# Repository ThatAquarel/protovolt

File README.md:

[![ProtoV MINI][cover]][website]

# A power supply to catalyze prototyping

[![Release][release-badge]][release]
[![CI][ci-badge]][ci]
[![Chat][chat-badge]][chat]
[![Crowd Supply][cs-badge]][cs]

**ProtoV MINI** is a credit card-sized, dual-channel lab power supply for
electronics prototyping and field testing. It is powered by USB-C PD and runs
open firmware written in Rust.

## Getting Started

Start with the [quick-start guide](docs/quick_start.md) to connect a USB-C PD
power supply, optionally link ProtoV MINI to a computer, and open
[ProtoV App](https://protov.app).

## Development

```sh
git clone https://github.com/flakeblade/protov.git
cd protov
rustup target add thumbv6m-none-eabi
cargo install just
just build
```
See [development](#development-1) for prerequisites, tests, and common
commands. Run `just --list` to see every available recipe.

## Documentation

### Guides

- [Device overview](docs/product.md) — hardware overview, and dimensions
- [Quick start](docs/quick_start.md) — quickstart wiring guide
- [Interface guide](docs/interface_guide.md) — normal UI flow with example screens
- [Troubleshooting](docs/troubleshooting.md) — faults, protection, and boot failures

### Development

Project structure
- [Repository index, and workspace modules](docs/repository.md)
- [Firmware roadmap](docs/roadmap.md)

Installation, building, and uploading
1. [Toolchain installation, and building](docs/development.md)
2. [Release bundling, and firmware signature](docs/releases.md)
3. [Flashing to hardware](docs/flashing.md)

### References

Hardware compatibility
- [Power delivery sources](docs/compatibility.md)
- [Breadboards](docs/compatibility.md)

Design documentation
- [Hardware and dimensions](docs/hardware.md)
- [SCPI protocol reference](protov-scpi/PROTOCOL.md)

Support
- [Troubleshooting](docs/troubleshooting.md)

<!-- - [Product overview](docs/product.md)
    
- [Flashing](docs/flashing.md)

- [SCPI protocol](protov-scpi/PROTOCOL.md)
- [SCPI crate](protov-scpi/README.md)
- [Bootloader](protov-bootloader/README.md)
- [Flash layout and firmware verification](protov-nvm/README.md) -->

## Contributing

Bug reports and contributions are welcome in the
[GitHub repository](https://github.com/flakeblade/protov).

> [!WARNING]
> Modifying or uploading firmware is done entirely at your own risk. An
> incompatible image can leave the device inoperable and may require USB
> BOOTSEL or SWD recovery. Bypassing current, voltage, temperature, power, or
> other protection limits can damage ProtoV MINI, connected equipment, or
> wiring and may create an electrical or fire hazard. Verify the hardware
> revision, understand every safety-related change, and test conservatively.

## License

[Eclipse Public License 2.0](LICENSE) © Alex Xia — [@ThatAquarel](http://github.com/thataquarel)

<p align="center">
  
  <br>
  A Flake &amp; Blade Robotics Design project
</p>

[fbrd]: https://flakeblade.com
[release-badge]: https://github.com/flakeblade/protov/actions/workflows/release.yml/badge.svg
[release]: https://github.com/flakeblade/protov/actions/workflows/release.yml
[ci-badge]: https://github.com/flakeblade/protov/actions/workflows/ci.yml/badge.svg
[ci]: https://github.com/flakeblade/protov/actions/workflows/ci.yml
[chat-badge]: https://img.shields.io/badge/chat-discussions-success.svg
[chat]: https://github.com/flakeblade/protov/discussions
[cs-badge]: https://img.shields.io/badge/Crowd-Supply-099?labelColor=555
[cs]: https://www.crowdsupply.com/flake-and-blade-robotics-design/protov-mini
[cover]: docs/res/logo/protov_mini_cover.svg
[website]: https://protov.app

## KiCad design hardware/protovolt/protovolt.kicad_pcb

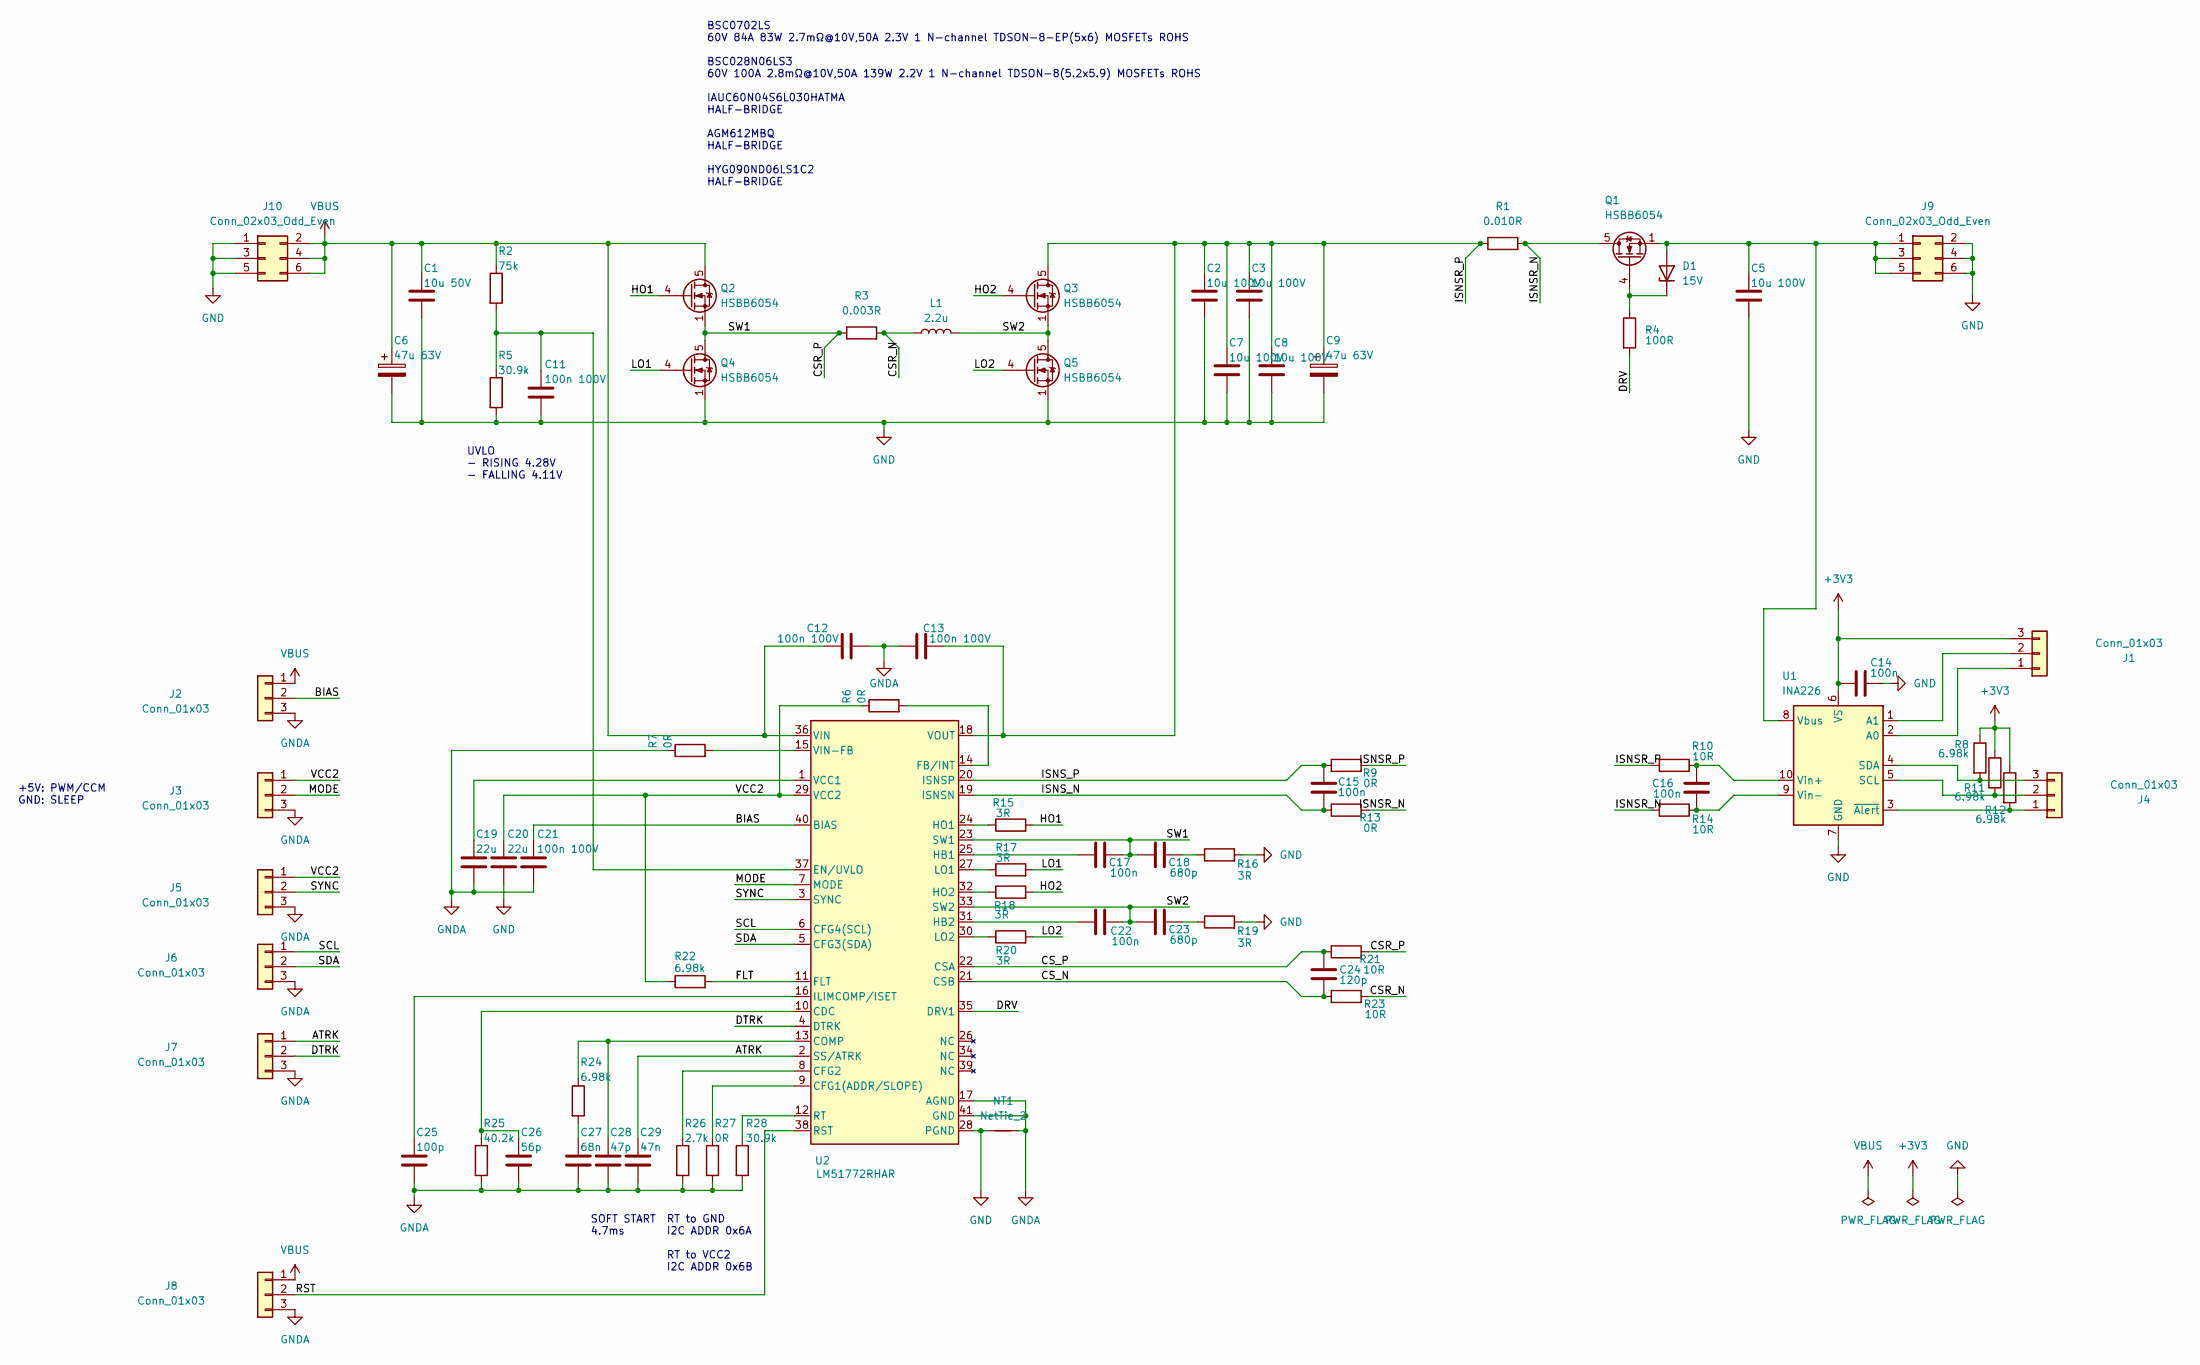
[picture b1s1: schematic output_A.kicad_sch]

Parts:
C1: 10u 50V; C_0805_2012Metric; LCSC C440198
C2, C3, C5, C7, C8: 10u 100V; C_1210_3225Metric; LCSC C5156756
C6, C9: 47u 63V; CP_Elec_8x10.5; LCSC C5246568
C11, C12, C13, C21: 100n 100V; C_0402_1005Metric; LCSC C162178
C14, C15, C16, C17, C22: 100n; C_0402_1005Metric; LCSC C77020
C18, C23: 680p; C_0402_1005Metric; LCSC C107030
C19, C20: 22u; C_0402_1005Metric; LCSC C3845593
C24: 120p; C_0402_1005Metric; LCSC C440165
C25: 100p; C_0402_1005Metric; LCSC C1546
C26: 56p; C_0402_1005Metric; LCSC C1572
C27: 68n; C_0402_1005Metric; LCSC C354977
C28: 47p; C_0402_1005Metric; LCSC C1567
C29: 47n; C_0402_1005Metric; LCSC C82219
D1: 15V; D_SOD-523; LCSC C131800
J1, J2, J3, J4, J5, J6, J7, J8: Conn_01x03; PinHeader_1x03_P2.54mm_Vertical_SMD_Pin1Left; LCSC C2883760
J9, J10: Conn_02x03_Odd_Even; PinHeader_2x03_P2.54mm_Vertical_SMD; LCSC C3294461
L1: 2.2u; L_Changjiang_FXL1050; LCSC C5359259
NT1: NetTie_2; NetTie-2_SMD_Pad0.5mm
Q1, Q2, Q3, Q4, Q5: HSBB6054; Diodes_PowerDI3333-8; LCSC C5341686
R1: 0.010R; R_2512_6332Metric_SHUNT; LCSC C393070
R2: 75k; R_0402_1005Metric; LCSC C286566
R3: 0.003R; R_2512_6332Metric_SHUNT; LCSC C326610
R4: 100R; R_0402_1005Metric; LCSC C25138
R5, R28: 30.9k; R_0402_1005Metric; LCSC C310222
R6, R7, R9, R13, R27: 0R; R_0402_1005Metric; LCSC C21376
R8, R11, R12, R22, R24: 6.98k; R_0402_1005Metric; LCSC C47500
R10, R14, R21, R23: 10R; R_0402_1005Metric; LCSC C25139
R15, R16, R17, R18, R19, R20: 3R; R_0402_1005Metric; LCSC C321179
R25: 40.2k; R_0402_1005Metric; LCSC C25893
R26: 2.7k; R_0402_1005Metric; LCSC C25885
U1: INA226; VSSOP-10_3x3mm_P0.5mm; LCSC C49851
U2: LM51772RHAR; QFN-40-1EP_6x6mm_P0.5mm_EP4.6x4.6mm_ThermalVias; LCSC C41383743

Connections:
+3V3: C14.1, J1.3, R8.1, R11.1, R12.1, U1.6 (VS)
/output_A/ATRK: C29.1, J7.1, U2.2 (SS/ATRK)
/output_A/BIAS: C21.2, J2.2, U2.40 (BIAS)
/output_A/CSR_N: L1.1, R3.2, R23.2
/output_A/CSR_P: C17.2, C18.1, Q2.1 (S), Q2.2 (S), Q2.3 (S), Q4.5 (D), R3.1, R21.2, U2.23 (SW1)
/output_A/CS_N: C24.2, R23.1, U2.21 (CSB)
/output_A/CS_P: C24.1, R21.1, U2.22 (CSA)
/output_A/DRV: R4.2, U2.35 (DRV1)
/output_A/DTRK: J7.2, U2.4 (DTRK)
/output_A/FLT: R22.2, U2.11 (FLT)
/output_A/HO1: Q2.4 (G), R15.2
/output_A/HO2: Q3.4 (G), R18.2
/output_A/ISNSR_N: Q1.5 (D), R1.2, R13.2, R14.2
/output_A/ISNSR_P: C2.1, C3.1, C7.1, C8.1, C9.1, C13.1, Q3.5 (D), R1.1, R9.2, R10.2, U2.18 (VOUT)
/output_A/ISNS_N: C15.1, R13.1, U2.19 (ISNSN)
/output_A/ISNS_P: C15.2, R9.1, U2.20 (ISNSP)
/output_A/LO1: Q4.4 (G), R17.2
/output_A/LO2: Q5.4 (G), R20.2
/output_A/MODE: J3.2, U2.7 (MODE)
/output_A/RST: J8.2, U2.38 (RST)
/output_A/SCL: J6.1, U2.6 (CFG4(SCL))
/output_A/SDA: J6.2, U2.5 (CFG3(SDA))
/output_A/SW2: C22.2, C23.1, L1.2, Q3.1 (S), Q3.2 (S), Q3.3 (S), Q5.5 (D), U2.33 (SW2)
/output_A/SYNC: J5.2, U2.3 (SYNC)
/output_A/VCC2: C20.1, J3.1, J5.1, R6.1, R22.1, U2.29 (VCC2)
GND: C1.2, C2.2, C3.2, C5.2, C6.2, C7.2, C8.2, C9.2, C11.1, C14.2, C20.2, J9.2, J9.4, J9.6, J10.1, J10.3, J10.5, NT1.1, Q4.1 (S), Q4.2 (S), Q4.3 (S), Q5.1 (S), Q5.2 (S), Q5.3 (S), R5.2, R16.2, R19.2, U1.7 (GND), U2.28 (PGND)
GNDA: C12.1, C13.2, C19.2, C21.1, C25.2, C26.2, C27.2, C28.2, C29.2, J2.3, J3.3, J5.3, J6.3, J7.3, J8.3, NT1.2, R7.1, R25.2, R26.2, R27.2, R28.2, U2.17 (AGND), U2.41 (GND)
unnamed: C18.2, R16.1
unnamed: C23.2, R19.1
unnamed: C27.1, R24.2
unnamed: C5.1, D1.2 (A), J9.1, J9.3, J9.5, Q1.1 (S), Q1.2 (S), Q1.3 (S), U1.8 (Vbus)
unnamed: D1.1 (K), Q1.4 (G), R4.1
unnamed: J1.1, U1.2 (A0)
unnamed: J1.2, U1.1 (A1)
unnamed: J4.1, R12.2, U1.3 (~Alert)
unnamed: J4.2, R11.2, U1.5 (SCL)
unnamed: J4.3, R8.2, U1.4 (SDA)
unnamed: C16.1, R10.1, U1.10 (Vin+)
unnamed: C16.2, R14.1, U1.9 (Vin-)
unnamed: C26.1, R25.1, U2.10 (CDC)
unnamed: R27.1, U2.9 (CFG1(ADDR/SLOPE))
unnamed: R26.1, U2.8 (CFG2)
unnamed: C28.1, R24.1, U2.13 (COMP)
unnamed: C11.2, R2.2, R5.1, U2.37 (EN/UVLO)
unnamed: R6.2, U2.14 (FB/INT)
unnamed: C17.1, U2.25 (HB1)
unnamed: C22.1, U2.31 (HB2)
unnamed: R15.1, U2.24 (HO1)
unnamed: R18.1, U2.32 (HO2)
unnamed: C25.1, U2.16 (ILIMCOMP/ISET)
unnamed: R17.1, U2.27 (LO1)
unnamed: R20.1, U2.30 (LO2)
unnamed: R28.1, U2.12 (RT)
unnamed: C19.1, U2.1 (VCC1)
unnamed: R7.2, U2.15 (VIN-FB)
VBUS: C1.1, C6.1, C12.2, J2.1, J8.1, J10.2, J10.4, J10.6, Q2.5 (D), R2.1, U2.36 (VIN)

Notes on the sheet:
UVLO - RISING 4.28V - FALLING 4.11V
+5V: PWM/CCM GND: SLEEP
SOFT START 4.7ms
BSC0702LS 60V 84A 83W 2.7mΩ@10V,50A 2.3V 1 N-channel TDSON-8-EP(5x6) MOSFETs ROHS BSC028N06LS3 60V 100A 2.8mΩ@10V,50A 139W 2.2V 1 N-channel TDSON-8(5.2x5.9) MOSFETs ROHS IAUC60N04S6L030HATMA HALF-BRIDGE AGM612MBQ HALF-BRIDGE HYG090ND06LS1C2 HALF-BRIDGE
RT to GND I2C ADDR 0x6A RT to VCC2 I2C ADDR 0x6B

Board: 4 copper layers, 75 parts (0 on the bottom side), 56 nets, no tracks yet.

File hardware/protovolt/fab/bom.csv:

"Id";"Designator";"Footprint";"Quantity";"Designation";"Supplier and ref";
1;"R4";"R_0402_1005Metric";1;"100R";;;
2;"J2,J8,J3,J4,J5,J7,J6,J1";"PinHeader_1x03_P2.54mm_Vertical_SMD_Pin1Left";8;"Conn_01x03";;;
3;"C29";"C_0402_1005Metric";1;"47n";;;
4;"J9,J10";"PinHeader_2x03_P2.54mm_Vertical_SMD";2;"Conn_02x03_Odd_Even";;;
5;"R19,R18,R17,R15,R16,R20";"R_0402_1005Metric";6;"3R";;;
6;"C23,C18";"C_0603_1608Metric";2;"680p";;;
7;"C20,C19";"C_0603_1608Metric";2;"22u";;;
8;"C13,C21,C11,C12";"R_0603_1608Metric";4;"100n 100V";;;
9;"Q1,Q4,Q5,Q3,Q2";"TDSON-8-1";5;"BSC0702LS";;;
10;"C5,C2,C7,C8,C4,C1,C3";"C_1210_3225Metric";7;"10u 100V";;;
11;"C27";"C_0402_1005Metric";1;"68n";;;
12;"R6,R9,R13,R27,R7";"R_0402_1005Metric";5;"0R";;;
13;"C16,C17,C22,C15,C14";"C_0603_1608Metric";5;"100n";;;
14;"R5,R28";"R_0402_1005Metric";2;"30.9k";;;
15;"C28";"C_0402_1005Metric";1;"47p";;;
16;"L1";"L_Changjiang_FXL1050";1;"2.2u";;;
17;"R1";"R_2512_6332Metric";1;"0.010R";;;
18;"R11,R22,R8,R12,R24";"R_0402_1005Metric";5;"6.98k";;;
19;"U1";"VSSOP-10_3x3mm_P0.5mm";1;"INA226";;;
20;"R26";"R_0402_1005Metric";1;"2.7k";;;
21;"U2";"QFN-40-1EP_6x6mm_P0.5mm_EP4.6x4.6mm_ThermalVias";1;"LM51772RHAR";;;
22;"R25";"R_0402_1005Metric";1;"40.2k";;;
23;"R21,R10,R14,R23";"R_0402_1005Metric";4;"10R";;;
24;"R2";"R_0402_1005Metric";1;"75k";;;
25;"R3";"R_1206_3216Metric";1;"0.003R";;;
26;"C24";"C_0402_1005Metric";1;"120p";;;
27;"D1";"D_SOD-123";1;"15V";;;
28;"C10,C9,C6";"CP_Elec_8x11.9";3;"39u 50V";;;
29;"C25";"C_0402_1005Metric";1;"100p";;;
30;"C26";"C_0402_1005Metric";1;"56p";;;

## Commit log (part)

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2025-05-11 kicad .gitignore
2025-05-11 add file to .gitignore
2025-05-11 LM51772 buck/boost base
2025-05-14 finish demo schematic
2025-05-15 route h-bridge
2025-05-15 fet routing
2025-05-16 four layer
2025-05-16 wire all
2025-05-16 route ground
2025-05-17 finalize DRU & PCB
2025-05-17 pnp files
2025-05-17 replace parts
2025-05-18 retrace all
2025-05-18 add BOM
2025-05-18 add basic parts
2025-05-19 order batch
2025-05-19 cleanup source
2025-05-19 implement TPS55289
2025-06-03 mini
2025-06-05 add interface & RP2040
2025-06-07 RP2040 boilerplate + INA226
2025-06-07 boost converter management
2025-06-07 render on screen test
2025-06-08 interface
2025-06-08 finalize parts in schematic
2025-06-09 route most
2025-06-09 ERC run
2025-06-09 assign footprints & LCSC id
2025-06-09 build all footprints
2025-06-09 import to PCB
2025-06-09 place ui elements
2025-06-10 route power stage
2025-06-10 route
2025-06-11 route digitals
2025-06-11 place all parts
2025-06-11 route simple traces
2025-06-11 route sense lines
2025-06-12 put FPC to front & rearrange buck/boost
2025-06-12 route power
2025-06-14 reroute all except 3V3 & GND
2025-06-16 finish routing
2025-06-16 all DRC except silkscreen warnings
2025-06-16 fix diode footprint
2025-06-16 finalize routing
2025-06-16 add logo
2025-06-16 cleanup schematic
2025-06-18 refactor
2025-06-21 first draft
2025-06-21 first display
2025-06-21 dynamic text render without clear
2025-06-21 first fab run
2025-06-21 add transparent logo
2025-06-22 ui rendering + updating
2025-06-22 simplify controls drawing
2025-06-22 temporary dev directory
2025-06-22 cleanup imports
2025-06-22 basic docs
2025-06-22 use framebuf
2025-06-22 channel toggle
2025-06-23 refactor ui + panic
2025-06-23 draw measurements
2025-06-23 navbar
2025-06-23 navbar buttons
2025-06-23 buttons select
2025-06-23 change navbar icons order
2025-06-23 get default limits
2025-06-23 refactor tasks
2025-06-23 setpoint type switch
2025-06-23 sub measurement select
2025-06-23 v/i select
2025-06-23 left right navigation
2025-06-26 refactor + select modify state
2025-06-26 submeasurement selection
2025-06-27 setpoint modify without buffer & clamping
2025-06-28 adjust limits
2025-07-01 enable backlight
2025-07-01 button interfacing
2025-07-01 offload polling to core1
2025-07-08 add channel leds
2025-07-08 add other leds color
2025-07-08 move
2025-07-08 refactor i2c hal
2025-07-08 basic readout
2025-07-08 readout two's complement
2025-07-09 basic power systems
2025-07-09 basic output voltage level modification
2025-07-09 power discharge + current limiting
2025-07-27 Create LICENSE
2025-07-27 add info to readme
2025-07-27 flip channels & correct order
2025-07-28 switch converters
2025-07-28 remove kicad backups
2025-10-21 update logotype
2025-10-21 modify boot logo to ProtoV
2025-10-23 add demo boot screen feature
2025-10-23 calibrate TPS55289 output voltage
2025-10-23 change default USB-C PD standard
2025-11-07 new readme with CS link
2025-11-07 update readme with CS badge
2025-11-09 update crowdsupply logo
2025-11-09 change cs logo
2025-11-09 add more info tag
2025-11-23 initial setup of Tauri + React for ProtoV Desktop
2025-11-23 modify app structure
2025-11-23 add devices cards
2025-11-23 add disable all button
2025-11-23 invidiual devices channels
2025-11-23 controls panel
2026-01-22 base temperature measurement hal
2026-01-22 refactor sensing loops
2026-01-23 add current mode readback
2026-01-23 refactor & remove unused imports
2026-01-28 add channel header information tag
2026-06-26 add scpi interface through serial
2026-06-26 first interface with software
2026-06-27 increase task arena size & fix hardfault races on hardware channel mut
2026-06-27 add CC/CV identifier on top of screen
2026-06-27 add scpi color & refactor color settings
2026-06-27 add cc/cv/ocp/ovp/otp flag to navbar & mode SCPI interface
2026-06-27 consolidate configuration files
2026-06-27 refactor to add unit testing capabilities & divide into protov-core and protov-hal
2026-06-27 silence unused micromath import on x86 test build
2026-06-27 change thumbv6m target to default & add pkg uf2 command
2026-06-27 fix linter warnings & refactor imports
2026-06-27 add UI app flow unit tests
2026-06-27 fix target for github CI
2026-06-27 apply formatter
2026-06-28 remove refactored config files
2026-06-28 remove empty file
2026-06-28 remove useless file
2026-06-28 initial PDO negotiation using STUSB4500
2026-06-28 remove delays in negotiation
2026-06-28 allow priority for existing PD negotiation contracts
2026-06-28 fix compiler warnings, unused imports & dead code
2026-06-28 refactor PD negotiation algorithm
2026-06-28 add navbar status info & PD report
2026-06-28 rename to hardware revision
2026-06-28 add hardware revision distinction
2026-06-28 fix formatting issue
2026-06-28 Release v1.0.0: semver bump and tag-triggered firmware CI
2026-06-28 Release v1.0.1: bump & setup elf2uf2 build on CI
2026-06-29 update protov-core for simulator
2026-06-29 add protov-hal-mock simulator over ws
2026-06-29 add protov-hal-mock testing CI
2026-06-29 fix clippy return Error
2026-06-29 add integrative checks
2026-06-29 add assigned PID 0x112B from RPI
2026-06-29 add disconnection schemes to mock hal
2026-06-29 bump to v1.2.1 hal update & fmt
2026-06-29 add settings page display
2026-06-29 format
2026-06-29 bump to v1.3.0
2026-06-30 refactor USB CDC-ACM packages
